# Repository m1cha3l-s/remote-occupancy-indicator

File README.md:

# Remote occupancy indicator

ESP32 based occupancy marker for meeting rooms, office cubicles and etc. and a simple remote for it. ESP-NOW is used for communication between the the boards, which are using the ESP32-C3 Super Mini

## Assembling
1. Print the both the Indicator and Remote top and bottom parts in a filament of your choice
2. Print the LED part of the Indicator and Remote case in a transparent filament or white filament (not tested) so that the leds can shine through it.
3. Use super glue to put the LED Parts in place (on the inside) if they already don't hold in place, even if they do the super glue wouldn't hurt.
4. The top and bottom of both cases snap together, after you snap them together you can move one the Setup!
5. For mounting use command strips or heavy duty double sided tape!!

## Setup 
1. Select the ESP32 Super Mini in Arduino IDE
2. Flash the MAC-Finder to both the boards and write down the MAC Address which will be sent in the Serial Monitor
3. In the indicator firmware file change the broadcast MAC address to the one the remote gave you
4. Flash!
5. Now in the remote firmware file change the broadcast MAC address to the one the indicator gave you
6. Flash!
7. Now the Indicator and Remote will connect to each other automatically

## Looks

## PCB/Schematic

### BOM
| Part Name | Quantity | Price (USD) | Total (USD) | Link |
|---|---|---|---|---|
| ESP32-C3 Super Mini | 2 | 3.16 | 6.32 | https://www.aliexpress.com/item/1005005834458965.html |
| 20pcs SK6812MINI-E | 1 | 1.75 | 1.75 | https://www.aliexpress.com/item/1005008308801366.html |
| 20PCS Tact Push Button Switch 12V Copper 4Pin SMD Micro Switch 6X6X5mm | 1 | 1.62 | 1.62 | 	https://www.aliexpress.com/item/1005005834458965.html |
| Aliexpress shipping | 1 | 2.55 | 2.55 | |
| Custom PCB (with shipping) | 1 | 4.24 | 4.24 | jlcpcb |
| 3D Printed case | 1 | 0 | 0 | none - I have my own printer |
| Total ||| 16.48 |

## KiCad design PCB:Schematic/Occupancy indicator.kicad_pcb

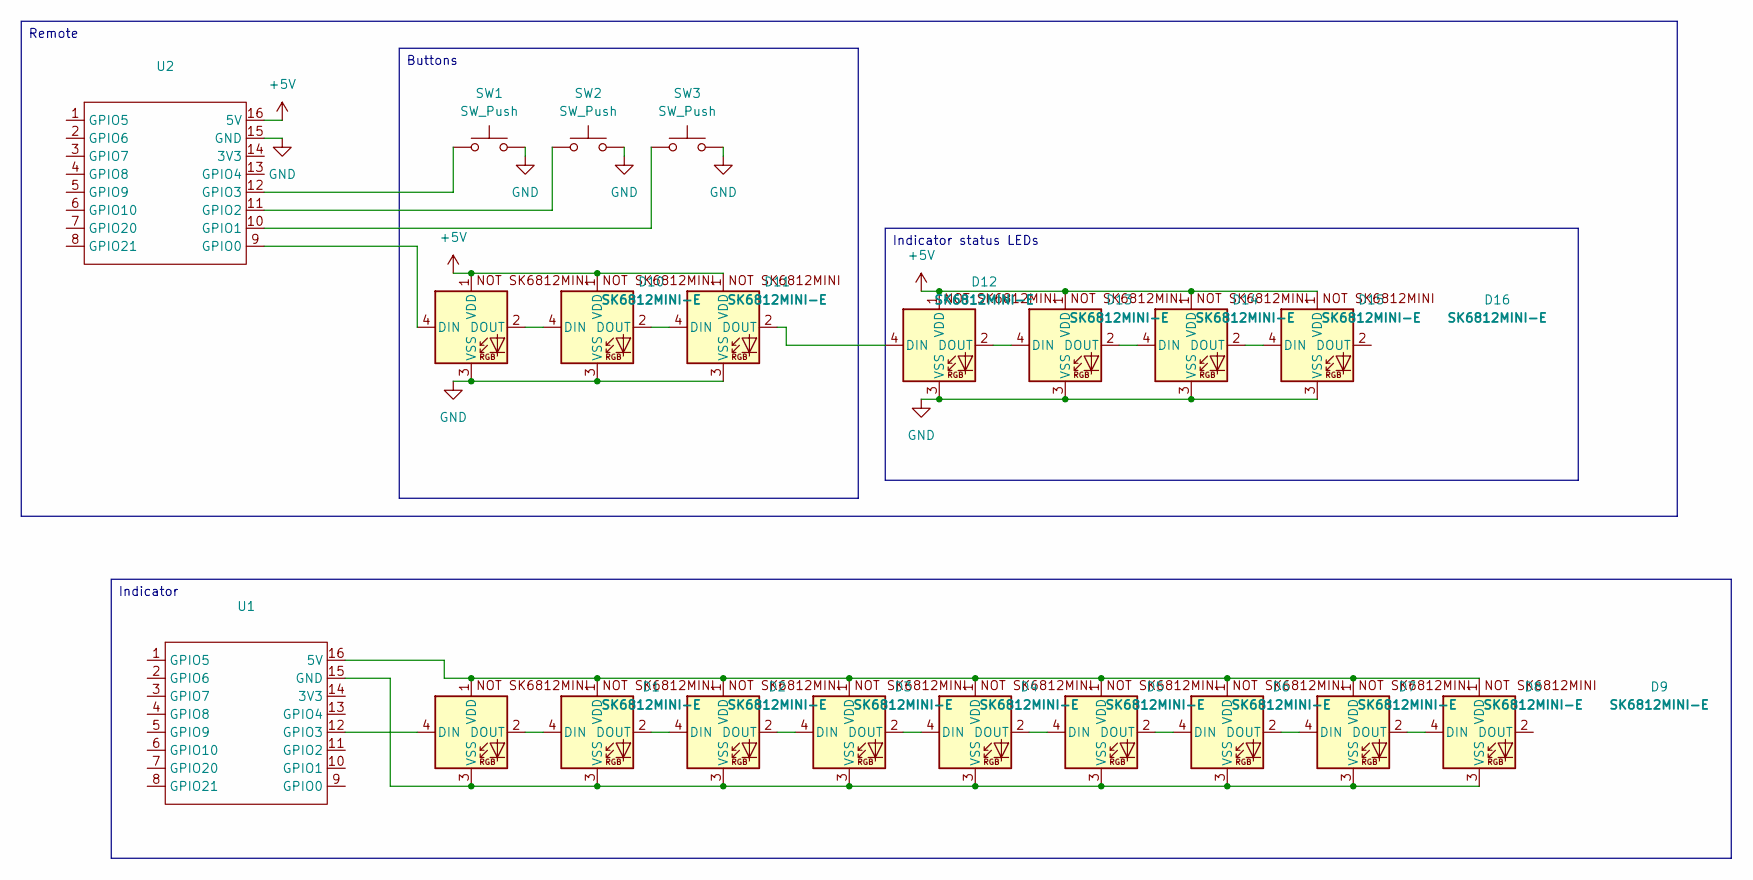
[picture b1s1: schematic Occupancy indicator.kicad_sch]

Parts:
D1, D2, D3, D4, D5, D6, D7, D8, D9, D10, D11, D12, D13, D14, D15, D16: SK6812MINI-E; SK6812MINI-E_fixed
SW1, SW2, SW3: SW_Push; SW_PUSH_6mm_H5mm
U1, U2: COMM-SMD_16P-L22.5-W18.0-P2.54-TL; Manufacturer Part ESP32C3-SuperMini; LCSC Part Name ESP32C3-SuperMini

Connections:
+5V: D10.1 (VDD), D11.1 (VDD), D12.1 (VDD), D13.1 (VDD), D14.1 (VDD), D15.1 (VDD), D16.1 (VDD), U2.16 (5V)
GND: D10.3 (VSS), D11.3 (VSS), D12.3 (VSS), D13.3 (VSS), D14.3 (VSS), D15.3 (VSS), D16.3 (VSS), SW1.2, SW2.2, SW3.2, U2.15 (GND)
unnamed: D1.4 (DIN), U1.12 (GPIO3)
unnamed: D1.2 (DOUT), D2.4 (DIN)
unnamed: D1.1 (VDD), D2.1 (VDD), D3.1 (VDD), D4.1 (VDD), D5.1 (VDD), D6.1 (VDD), D7.1 (VDD), D8.1 (VDD), D9.1 (VDD), U1.16 (5V)
unnamed: D1.3 (VSS), D2.3 (VSS), D3.3 (VSS), D4.3 (VSS), D5.3 (VSS), D6.3 (VSS), D7.3 (VSS), D8.3 (VSS), D9.3 (VSS), U1.15 (GND)
unnamed: D2.2 (DOUT), D3.4 (DIN)
unnamed: D3.2 (DOUT), D4.4 (DIN)
unnamed: D4.2 (DOUT), D5.4 (DIN)
unnamed: D5.2 (DOUT), D6.4 (DIN)
unnamed: D6.2 (DOUT), D7.4 (DIN)
unnamed: D7.2 (DOUT), D8.4 (DIN)
unnamed: D8.2 (DOUT), D9.4 (DIN)
unnamed: D10.4 (DIN), U2.9 (GPIO0)
unnamed: D10.2 (DOUT), D11.4 (DIN)
unnamed: D11.2 (DOUT), D12.4 (DIN)
unnamed: D12.2 (DOUT), D13.4 (DIN)
unnamed: D13.2 (DOUT), D14.4 (DIN)
unnamed: D14.2 (DOUT), D15.4 (DIN)
unnamed: D15.2 (DOUT), D16.4 (DIN)
unnamed: SW3.1, U2.10 (GPIO1)
unnamed: SW2.1, U2.11 (GPIO2)
unnamed: SW1.1, U2.12 (GPIO3)

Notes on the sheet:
Indicator status LEDs
Indicator
Buttons
Remote

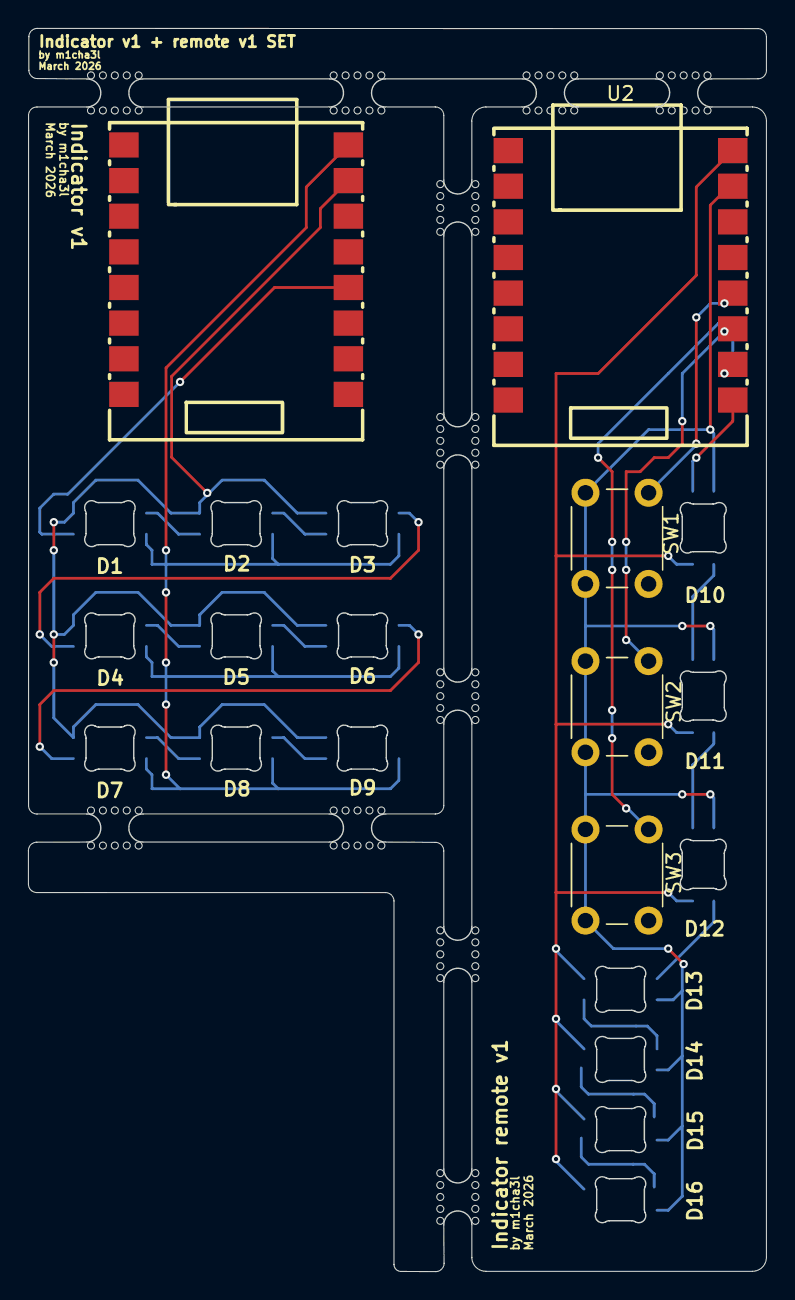
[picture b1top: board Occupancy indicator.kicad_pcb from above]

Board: 2 copper layers, 52.6 x 88.6 mm, 21 parts (0 on the bottom side), 23 nets.

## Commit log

2026-03-11 Added PCB/Schematic and gerber files
2026-03-12 Added MAC_Finder
    First part of the firmware to find MAC Address of the board for ESP-NOW code
2026-03-13 Firmware for Remote and Indicator
2026-03-16 Added Indicator case .f3d file
    Whole case as a assembly
2026-03-16 Added Indicator case parts
2026-03-16 removed .DS_Store
2026-03-16 Added Remote case files
2026-03-16 Added BOM
2026-03-16 Added pics for README
2026-03-24 Initial plan
2026-03-24 Fix firmware bugs and clean up code quality issues
    Agent-Logs-Url: https://github.com/m1cha3l-s/remote-occupancy-indicator/sessions/370c4d6e-64f8-4acf-8383-43caac956e9a
2026-03-24 Added new firmware for indicator
2026-04-21 wroking
